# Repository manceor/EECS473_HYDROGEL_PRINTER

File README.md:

# Software Setup Guide

## Flashing the ATmega1284P through USB

To program the ATmega1284P, install download AVROSP.

This guide assumes that you have AVROSP added to your PATH.

1) When you first plug in the board

2) Hold RESET and SW0

3) Let go of RESET

4) Let go of SW0

5) In the terminal, enter the command "mode comx baud=57600 parity=n data=8".
    Replace the "x" in "comx" with the COM port that your board is plugged into.
    This can be found in the "Device Manager" on windows (AVR only supports COM ports 1-8)

6) In the folder where your .hex file is, run the following command:
    "AVROSP -dATmega1284P -cCOMx -pf -vf -if "filename.hex" -e".

## Setting up Atmel Studio for board programming

Install Atmel Studio 7

From fresh code:
Download TH3D Firmware <https://www.th3dstudio.com/knowledgebase/th3d-unified-firmware-package/>
Unzip into a folder of your choice, now referred to as "%TH3D DIRECTORY%"

1) New -> Project -> Create Project From Arduino Sketch

2) Create a new folder somewhere and select it

3) Sketch File:"%TH3D DIRECTORY%\TH3DUF_R2\Firmware\TH3DUF_R2\TH3DUF_R2.ino"

4) Arduino IDE Path: "%TH3D DIRECTORY%\TH3DUF_R2\Windows Arduino\"

5) To find the Marlin Code: see Arduino Core -> include -> variants

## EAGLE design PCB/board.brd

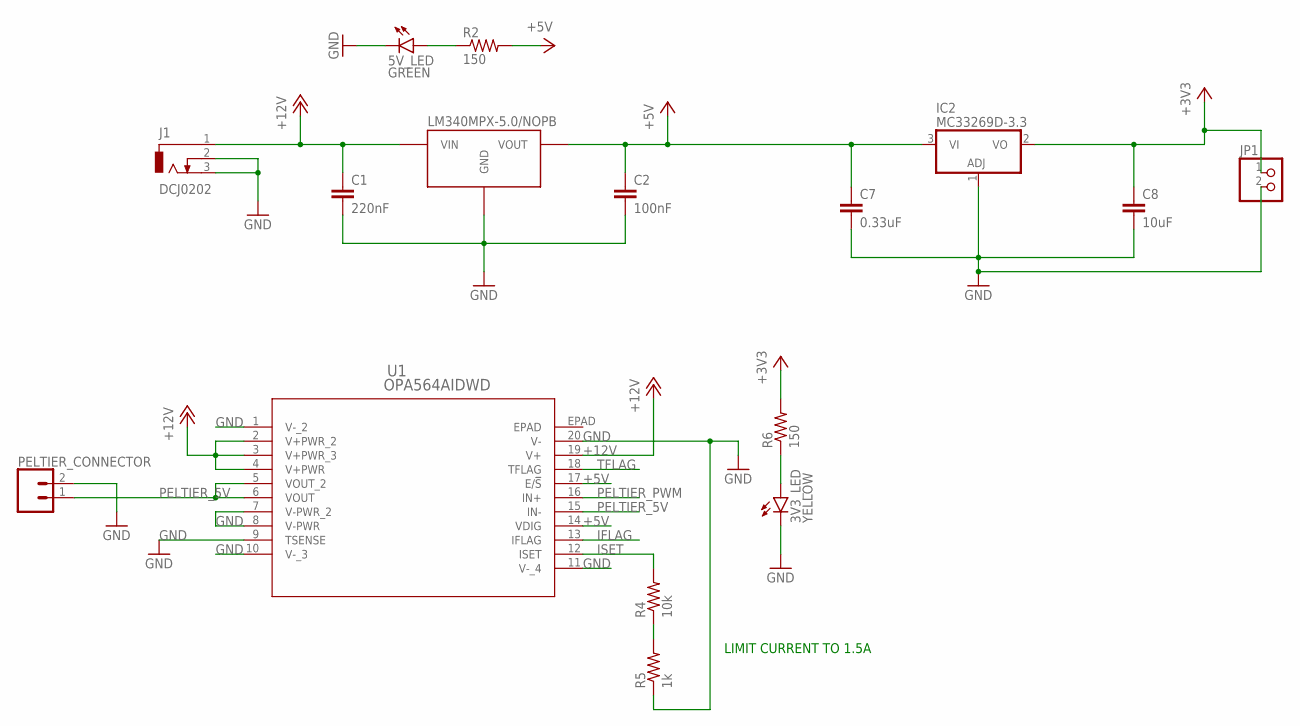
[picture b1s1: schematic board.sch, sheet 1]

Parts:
3V3_LED: YELLOW; CHIP-LED0603
5V_LED: GREEN; CHIP-LED0603
C1: 220nF; C0805
C2: 100nF; C0805
C7: 0.33uF; C0805
C8: 10uF; C0805
IC2: MC33269D-3.3; DPACK
J1: DCJ0202
JP1: PINHD-1X2; 1X02
LDO1: LM340MPX-5.0/NOPB; SOT-223
PELTIER_CONNECTOR: CONN_025MM; SCREWTERMINAL-5MM-2
R2, R6: 150; R0603
R4: 10k; R0603
R5: 1k; R0603
U1: OPA564AIDWD; DWD20_4P62X3P56

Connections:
+3V3: C8.1, IC2.2 (VO), JP1.1, R6.2
+5V: C2.1, C7.1, IC2.3 (VI), LDO1.P$3 (VOUT), R2.2, U1.14 (VDIG), U1.17 (E/!S); also elsewhere on the board
+12V: C1.1, J1.1, LDO1.P$1 (VIN), U1.2 (V+PWR_2), U1.3 (V+PWR_3), U1.4 (V+PWR), U1.19 (V+); also elsewhere on the board
GND: 3V3_LED.C, 5V_LED.C, C1.2, C2.2, C7.2, C8.2, IC2.1 (ADJ), J1.2, J1.3, JP1.2, LDO1.P$2 (GND), LDO1.P$4 (GND), PELTIER_CONNECTOR.2, R5.1, U1.1 (V-_2), U1.7 (V-PWR_2), U1.8 (V-PWR), U1.9 (TSENSE), U1.10 (V-_3), U1.11 (V-_4), U1.20 (V-); also elsewhere on the board
IFLAG: U1.13 (IFLAG); also elsewhere on the board
ISET: R4.2, U1.12 (ISET)
unnamed: 5V_LED.A, R2.1
unnamed: R4.1, R5.2
unnamed: 3V3_LED.A, R6.1
PELTIER_5V: PELTIER_CONNECTOR.1, U1.5 (VOUT_2), U1.6 (VOUT), U1.15 (IN-)
PELTIER_PWM: U1.16 (IN+); also elsewhere on the board
TFLAG: U1.18 (TFLAG); also elsewhere on the board

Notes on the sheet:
LIMIT CURRENT TO 1.5A

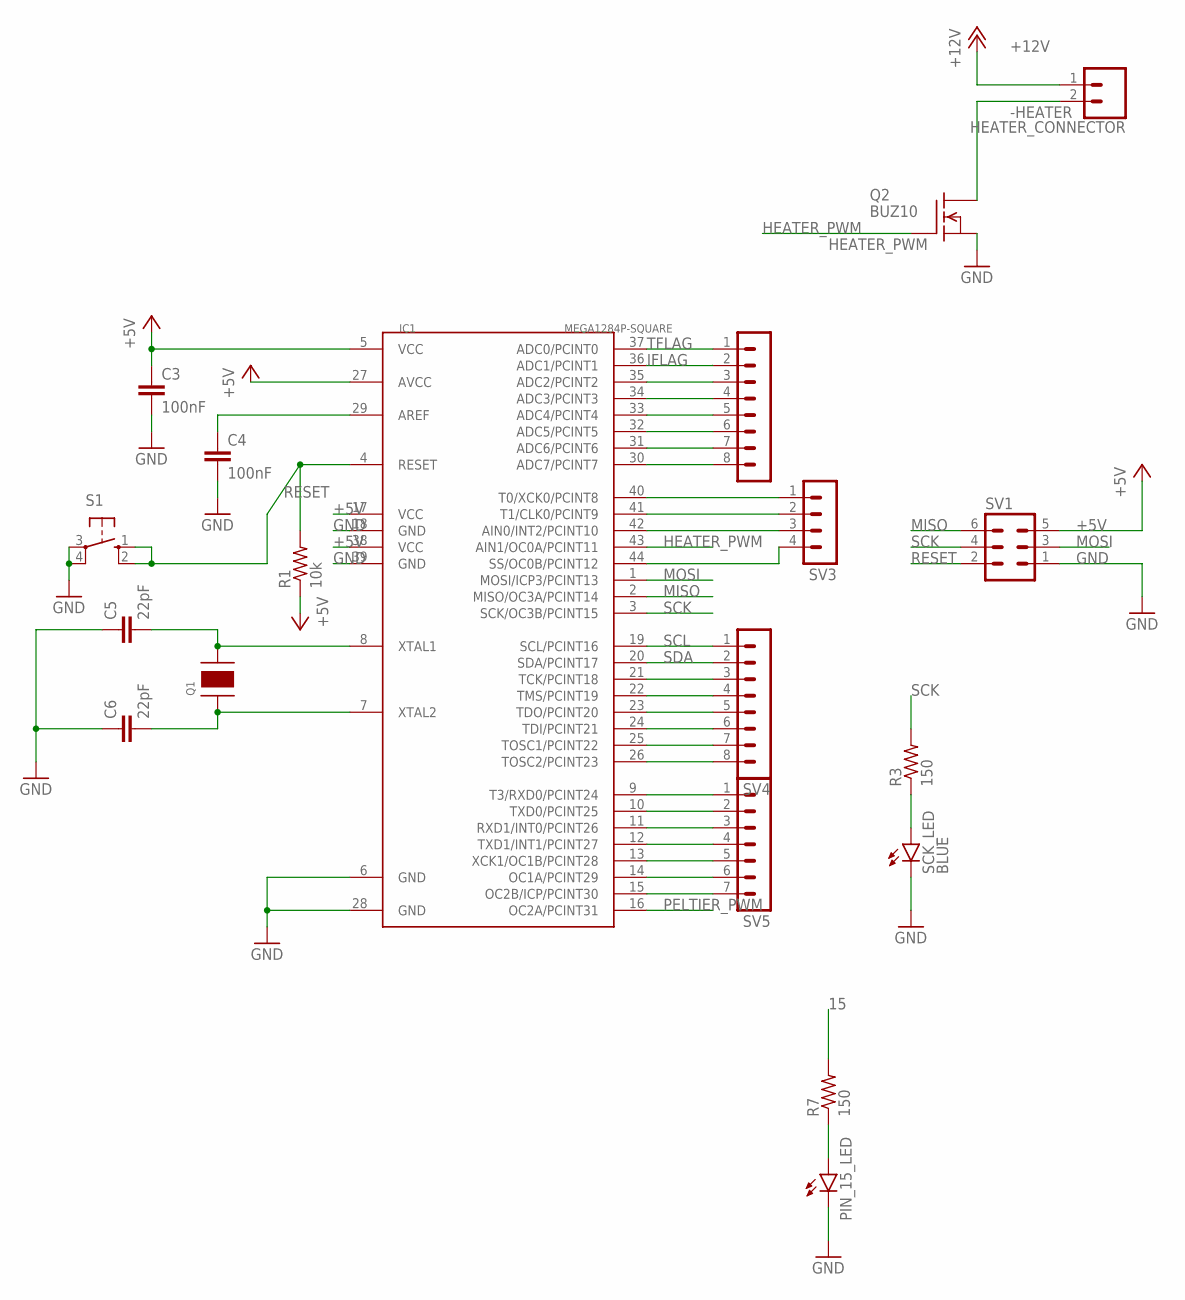
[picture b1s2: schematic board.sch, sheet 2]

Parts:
C3, C4: 100nF; C0603
C5, C6: 22pF; C0603
HEATER_CONNECTOR: CONN_025MM; SCREWTERMINAL-5MM-2
IC1: MEGA1284P-SQUARE; TQFP44
PIN_15_LED: BLUE; CHIP-LED0603
Q1: CRYSTAL_16MHZ_SMD; 4-SMD_DFN
Q2: BUZ10; TO220
R1: 10k; R0603
R3, R7: 150; R0603
S1: 10-XX; B3F-10XX
SCK_LED: BLUE; CHIP-LED0603
SV1: MA03-2
SV2, SV4: MA08-1
SV3: MA04-1
SV5: MA07-1

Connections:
9: IC1.9 (T3/RXD0/PCINT24), SV5.1
10: IC1.10 (TXD0/PCINT25), SV5.2
11: IC1.11 (RXD1/INT0/PCINT26), SV5.3
12: IC1.12 (TXD1/INT1/PCINT27), SV5.4
13: IC1.13 (XCK1/OC1B/PCINT28), SV5.5
14: IC1.14 (OC1A/PCINT29), SV5.6
15: IC1.15 (OC2B/ICP/PCINT30), R7.2, SV5.7
21: IC1.21 (TCK/PCINT18), SV4.3
22: IC1.22 (TMS/PCINT19), SV4.4
23: IC1.23 (TDO/PCINT20), SV4.5
24: IC1.24 (TDI/PCINT21), SV4.6
25: IC1.25 (TOSC1/PCINT22), SV4.7
26: IC1.26 (TOSC2/PCINT23), SV4.8
30: IC1.30 (ADC7/PCINT7), SV2.8
31: IC1.31 (ADC6/PCINT6), SV2.7
32: IC1.32 (ADC5/PCINT5), SV2.6
33: IC1.33 (ADC4/PCINT4), SV2.5
34: IC1.34 (ADC3/PCINT3), SV2.4
35: IC1.35 (ADC2/PCINT2), SV2.3
40: IC1.40 (T0/XCK0/PCINT8), SV3.1
41: IC1.41 (T1/CLK0/PCINT9), SV3.2
42: IC1.42 (AIN0/INT2/PCINT10), SV3.3
44: IC1.44 (SS/OC0B/PCINT12), SV3.4
+5V: C3.1, IC1.5 (VCC), IC1.17 (VCC), IC1.27 (AVCC), IC1.38 (VCC), R1.1, SV1.5; also elsewhere on the board
+12V: HEATER_CONNECTOR.1; also elsewhere on the board
-HEATER: HEATER_CONNECTOR.2, Q2.2 (D)
GND: C3.2, C4.2, C5.1, C6.1, IC1.6 (GND), IC1.18 (GND), IC1.28 (GND), IC1.39 (GND), PIN_15_LED.C, Q2.3 (S), S1.3, S1.4 (P1), SCK_LED.C, SV1.1; also elsewhere on the board
HEATER_PWM: IC1.43 (AIN1/OC0A/PCINT11), Q2.1 (G)
IFLAG: IC1.36 (ADC1/PCINT1), SV2.2; also elsewhere on the board
MISO: IC1.2 (MISO/OC3A/PCINT14), SV1.6
MOSI: IC1.1 (MOSI/ICP3/PCINT13), SV1.3
unnamed: PIN_15_LED.A, R7.1
unnamed: C4.1, IC1.29 (AREF)
unnamed: C5.2, IC1.8 (XTAL1), Q1.X2
unnamed: C6.2, IC1.7 (XTAL2), Q1.X1
unnamed: R3.1, SCK_LED.A
PELTIER_PWM: IC1.16 (OC2A/PCINT31); also elsewhere on the board
RESET: IC1.4 (RESET), R1.2, S1.1 (S), S1.2 (S1), SV1.2
SCK: IC1.3 (SCK/OC3B/PCINT15), R3.2, SV1.4
SCL: IC1.19 (SCL/PCINT16), SV4.1
SDA: IC1.20 (SDA/PCINT17), SV4.2
TFLAG: IC1.37 (ADC0/PCINT0), SV2.1; also elsewhere on the board

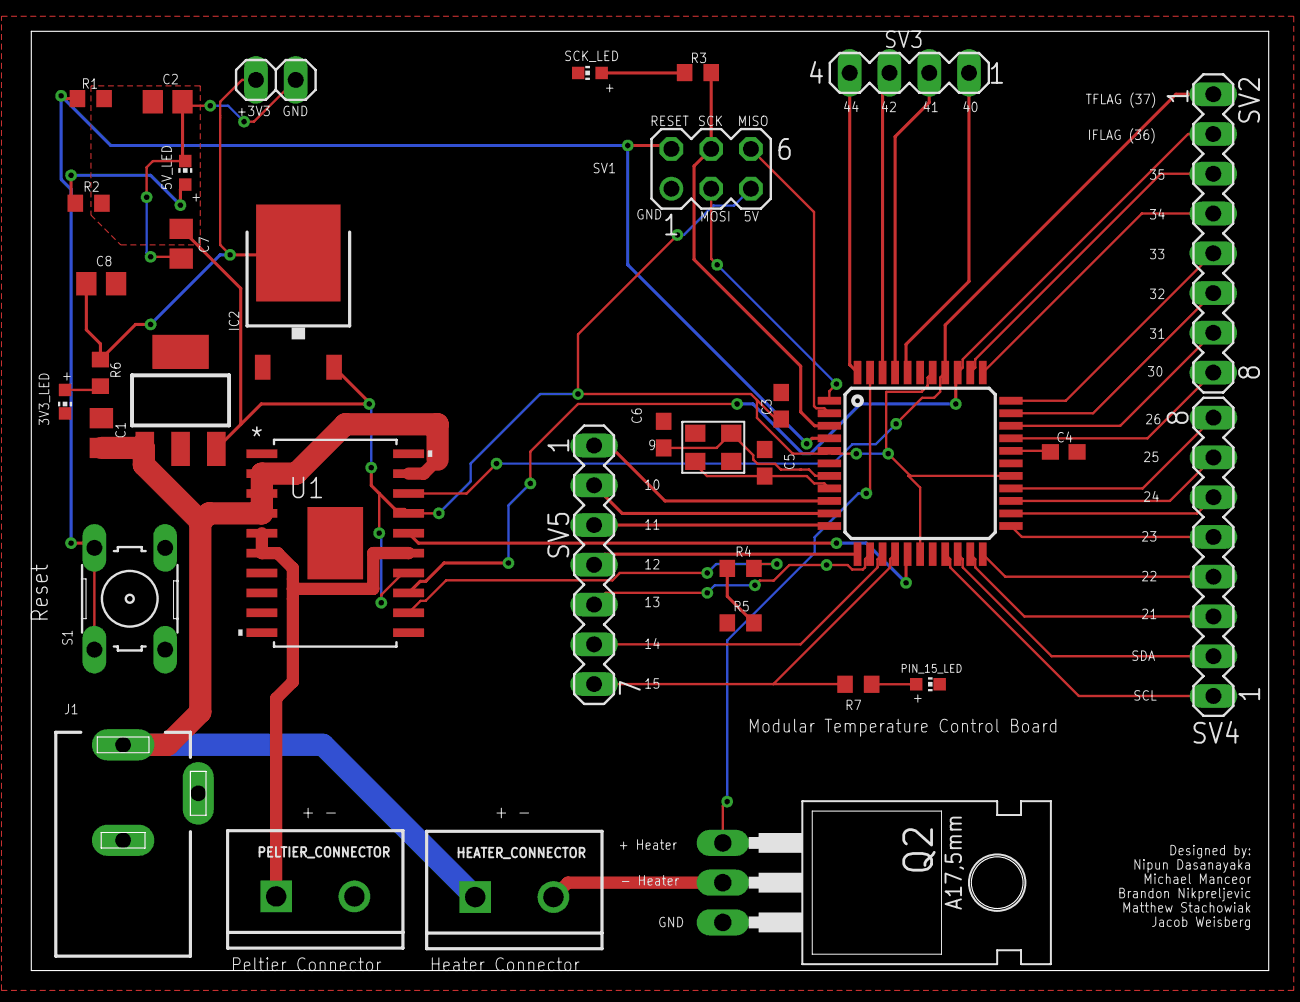
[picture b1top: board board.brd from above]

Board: 2 copper layers, 79.0 x 60.0 mm, 35 parts (0 on the bottom side), 48 nets.

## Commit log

2019-10-20 initial motor driver files with Arduino code
2019-10-21 added Atmel Studio 7 project containing motor code that works on the ATmega1284P
2019-10-21 Add README.md
2019-10-21 More README formatting
2019-10-21 Added AVROSP
2019-10-21 Fixed gitignore tracking vs settings
2019-10-21 Fixed gitignore
2019-10-21 Made first line a top level heading
2019-10-21 motor updates
2019-10-22 Add new directory
2019-10-22 Upload New File
2019-10-29 updated motor files for new controller
2019-10-31 Added instructions for setting up Atmel Studio
2019-11-07 Adding starter PCB files
2019-11-07 Nothing
2019-11-07 ADDING TH3D
2019-11-07 Adding TH3D Edits
2019-11-08 updated PCB with new LDO and PCB footprint
2019-11-09 Removed stupid shit Brandon put in
2019-11-11 G Code Add
2019-11-11 Fixed PCB stuff - main looking clean
2019-11-11 renamed file
2019-11-11 Fixed 3d Printing
2019-11-11 Added Op-Amp for peltier control and MOSFET for hot end cartridge heater control
2019-11-11 Adding simple Gcode and preheat material lcd cmds
2019-11-11 Made it 2 layers
2019-11-11 Added MOSFET for peltier control
2019-11-11 Finished connections for op-amp
2019-11-11 Fixed mosfet
2019-11-11 Added connector for heater
2019-11-12 Placing on board
2019-11-12 started routing
2019-11-12 finished routing PCB
2019-11-12 finished routing PCB with added pins; need silkscreen!
2019-11-14 Michael and Matthew, Silkscreening done
2019-11-14 Gerber Files Generated
2019-11-14 Finalized Board #1
2019-11-15 Made some adjustments to silkscreen placement

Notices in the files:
parts and their libraries:
SparkFun-Connectors: Licensing: Creative Commons ShareAlike 4.0 International - https://creativecommons.org/licenses/by-sa/4.0
